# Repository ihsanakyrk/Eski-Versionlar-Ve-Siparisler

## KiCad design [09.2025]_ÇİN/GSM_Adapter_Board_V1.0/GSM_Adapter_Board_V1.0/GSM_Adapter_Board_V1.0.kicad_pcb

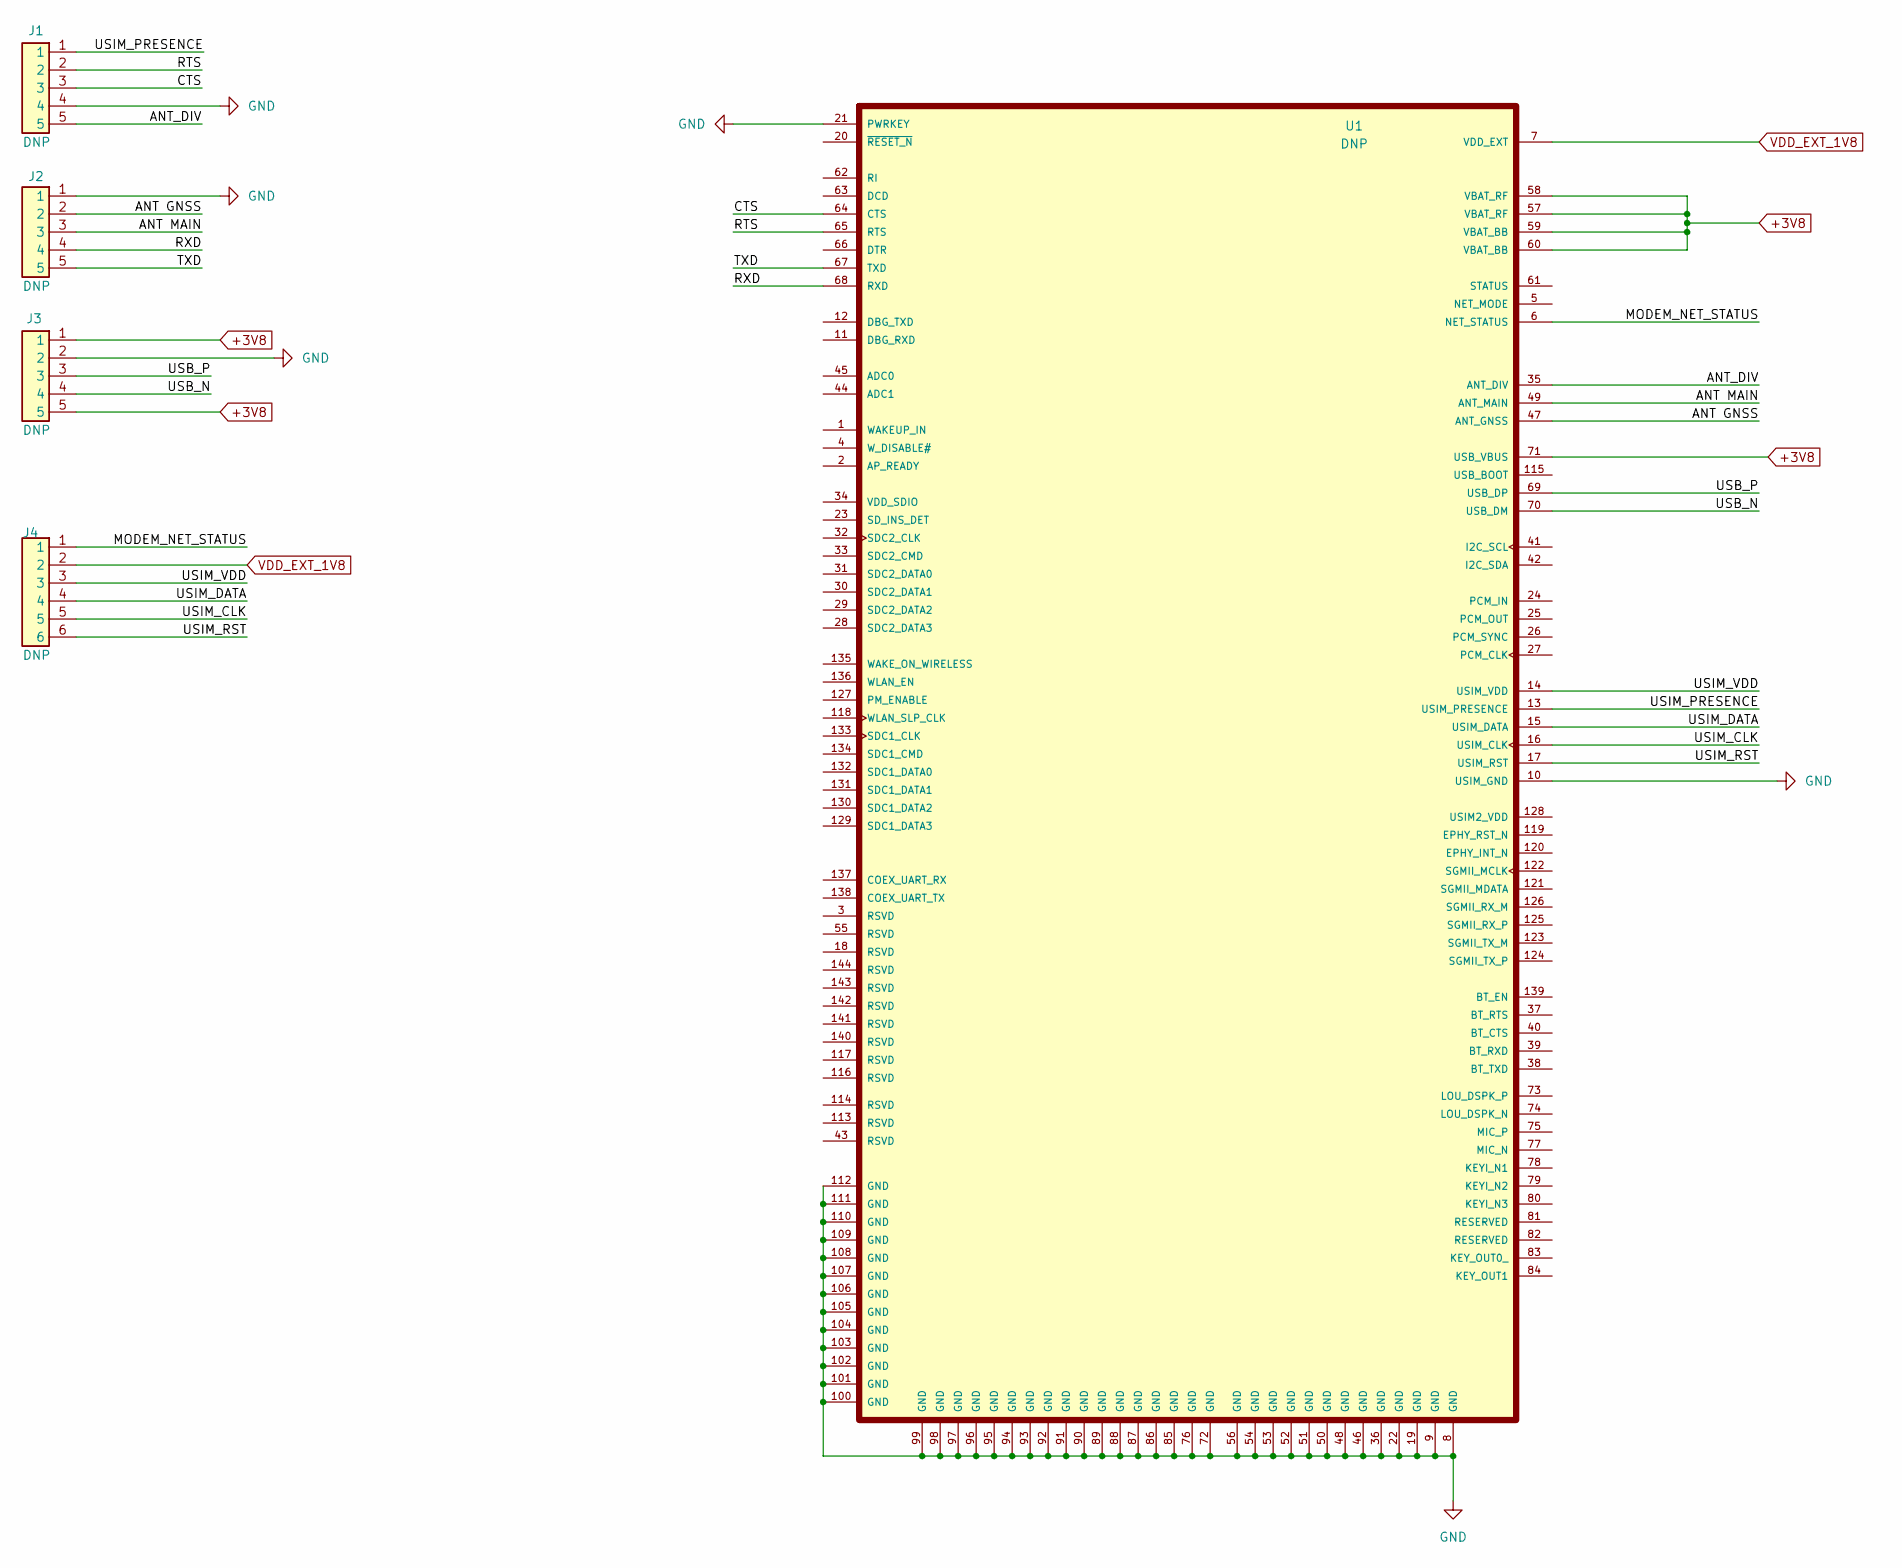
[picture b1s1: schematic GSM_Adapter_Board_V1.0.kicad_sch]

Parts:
J1, J2, J3: DNP; Castelled 5
J4: DNP; castelled 6
U1: DNP; GSM

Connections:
+3V8: J3.1, J3.5, U1.57 (VBAT_RF), U1.58 (VBAT_RF), U1.59 (VBAT_BB), U1.60 (VBAT_BB), U1.71 (USB_VBUS)
/ANT GNSS: J2.2, U1.47 (ANT_GNSS)
/ANT MAIN: J2.3, U1.49 (ANT_MAIN)
/ANT_DIV: J1.5, U1.35 (ANT_DIV)
/CTS: J1.3, U1.64 (CTS)
/MODEM_NET_STATUS: J4.1, U1.6 (NET_STATUS)
/RTS: J1.2, U1.65 (RTS)
/RXD: J2.4, U1.68 (RXD)
/TXD: J2.5, U1.67 (TXD)
/USB_N: J3.4, U1.70 (USB_DM)
/USB_P: J3.3, U1.69 (USB_DP)
/USIM_CLK: J4.5, U1.16 (USIM_CLK)
/USIM_DATA: J4.4, U1.15 (USIM_DATA)
/USIM_PRESENCE: J1.1, U1.13 (USIM_PRESENCE)
/USIM_RST: J4.6, U1.17 (USIM_RST)
/USIM_VDD: J4.3, U1.14 (USIM_VDD)
GND: J1.4, J2.1, J3.2, U1.8 (GND), U1.9 (GND), U1.10 (USIM_GND), U1.19 (GND), U1.21 (PWRKEY), U1.22 (GND), U1.36 (GND), U1.46 (GND), U1.48 (GND), U1.50 (GND), U1.51 (GND), U1.52 (GND), U1.53 (GND), U1.54 (GND), U1.56 (GND), U1.72 (GND), U1.76 (GND), U1.85 (GND), U1.86 (GND), U1.87 (GND), U1.88 (GND), U1.89 (GND), U1.90 (GND), U1.91 (GND), U1.92 (GND), U1.93 (GND), U1.94 (GND), U1.95 (GND), U1.96 (GND), U1.97 (GND), U1.98 (GND), U1.99 (GND), U1.100 (GND), U1.101 (GND), U1.102 (GND), U1.103 (GND), U1.104 (GND), U1.105 (GND), U1.106 (GND), U1.107 (GND), U1.108 (GND), U1.109 (GND), U1.110 (GND), U1.111 (GND), U1.112 (GND)
VDD_EXT_1V8: J4.2, U1.7 (VDD_EXT)

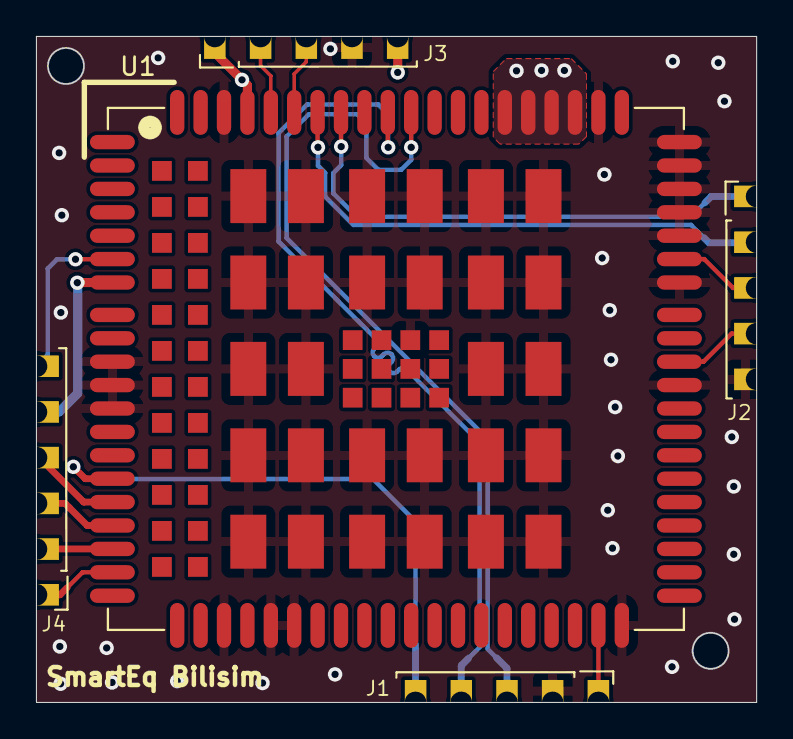
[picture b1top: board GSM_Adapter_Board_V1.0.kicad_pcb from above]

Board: 2 copper layers, 40.0 x 37.0 mm, 5 parts (0 on the bottom side), 18 nets.

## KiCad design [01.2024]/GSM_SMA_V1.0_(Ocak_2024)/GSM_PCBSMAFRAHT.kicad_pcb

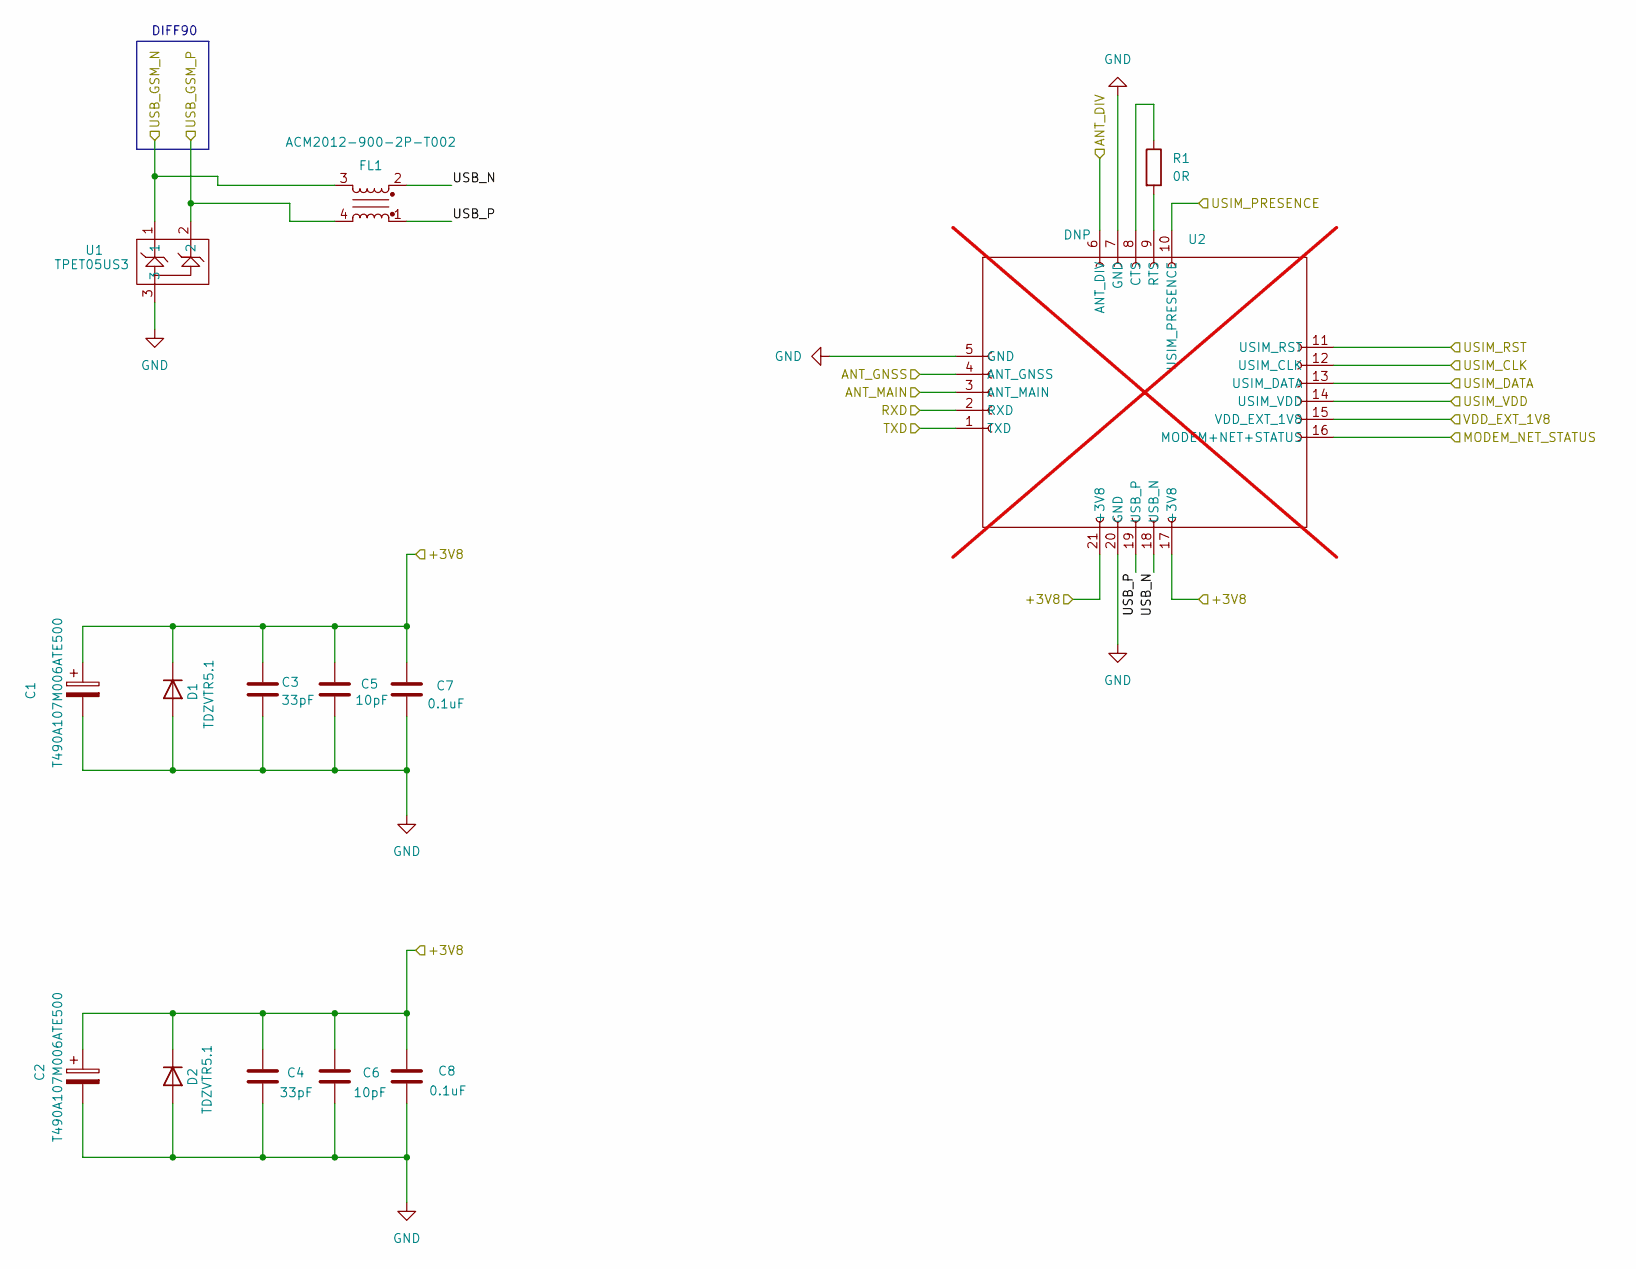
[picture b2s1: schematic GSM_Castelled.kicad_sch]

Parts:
C1, C2: T490A107M006ATE500; T490A; MPN T490A107M006ATE500
C3, C4: 33pF; C_0603_1608Metric
C5, C6: 10pF; C_0603_1608Metric
C7, C8: 0.1uF; C_0603_1608Metric
D1, D2: TDZVTR5.1; MPN TDZVTR5.1
FL1: ACM2012-900-2P-T002; MPN ACM2012-900-2P-T002
R1: 0R; R_0603_1608Metric
U1: TPET05US3; MPN TPET05US3
U2: DNP; GSM_Castelled; not fitted

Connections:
/91228-3002/MODEM_NET_STATUS: U2.16 (MODEM+NET+STATUS); also elsewhere on the board
/91228-3002/RXD: U2.2 (RXD); also elsewhere on the board
/91228-3002/TXD: U2.1 (TXD); also elsewhere on the board
/91228-3002/USB_GSM_N: FL1.3, U1.1; also elsewhere on the board
/91228-3002/USB_GSM_P: FL1.4, U1.2; also elsewhere on the board
/91228-3002/USIM_CLK: U2.12 (USIM_CLK); also elsewhere on the board
/91228-3002/USIM_DATA: U2.13 (USIM_DATA); also elsewhere on the board
/91228-3002/USIM_PRESENCE: U2.10 (USIM_PRESENCE); also elsewhere on the board
/91228-3002/USIM_RST: U2.11 (USIM_RST); also elsewhere on the board
/91228-3002/USIM_VDD: U2.14 (USIM_VDD); also elsewhere on the board
/91228-3002/VDD_EXT_1V8: U2.15 (VDD_EXT_1V8); also elsewhere on the board
/GSM_Castelled/+3V8: C1.1, C2.1, C3.1, C4.1, C5.1, C6.1, C7.1, C8.1, D1.1 (K), D2.1 (K), U2.17 (+3V8), U2.21 (+3V8); also elsewhere on the board
/GSM_Castelled/ANT_DIV: U2.6 (ANT_DIV); also elsewhere on the board
/GSM_Castelled/ANT_GNSS: U2.4 (ANT_GNSS); also elsewhere on the board
/GSM_Castelled/ANT_MAIN: U2.3 (ANT_MAIN); also elsewhere on the board
/GSM_Castelled/USB_N: FL1.2, U2.18 (USB_N)
/GSM_Castelled/USB_P: FL1.1, U2.19 (USB_P)
GND: C1.2, C2.2, C3.2, C4.2, C5.2, C6.2, C7.2, C8.2, D1.2 (A), D2.2 (A), U1.3, U2.5 (GND), U2.7 (GND), U2.20 (GND); also elsewhere on the board
unnamed: R1.1, U2.8 (CTS)
unnamed: R1.2, U2.9 (RTS)

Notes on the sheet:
DIFF90

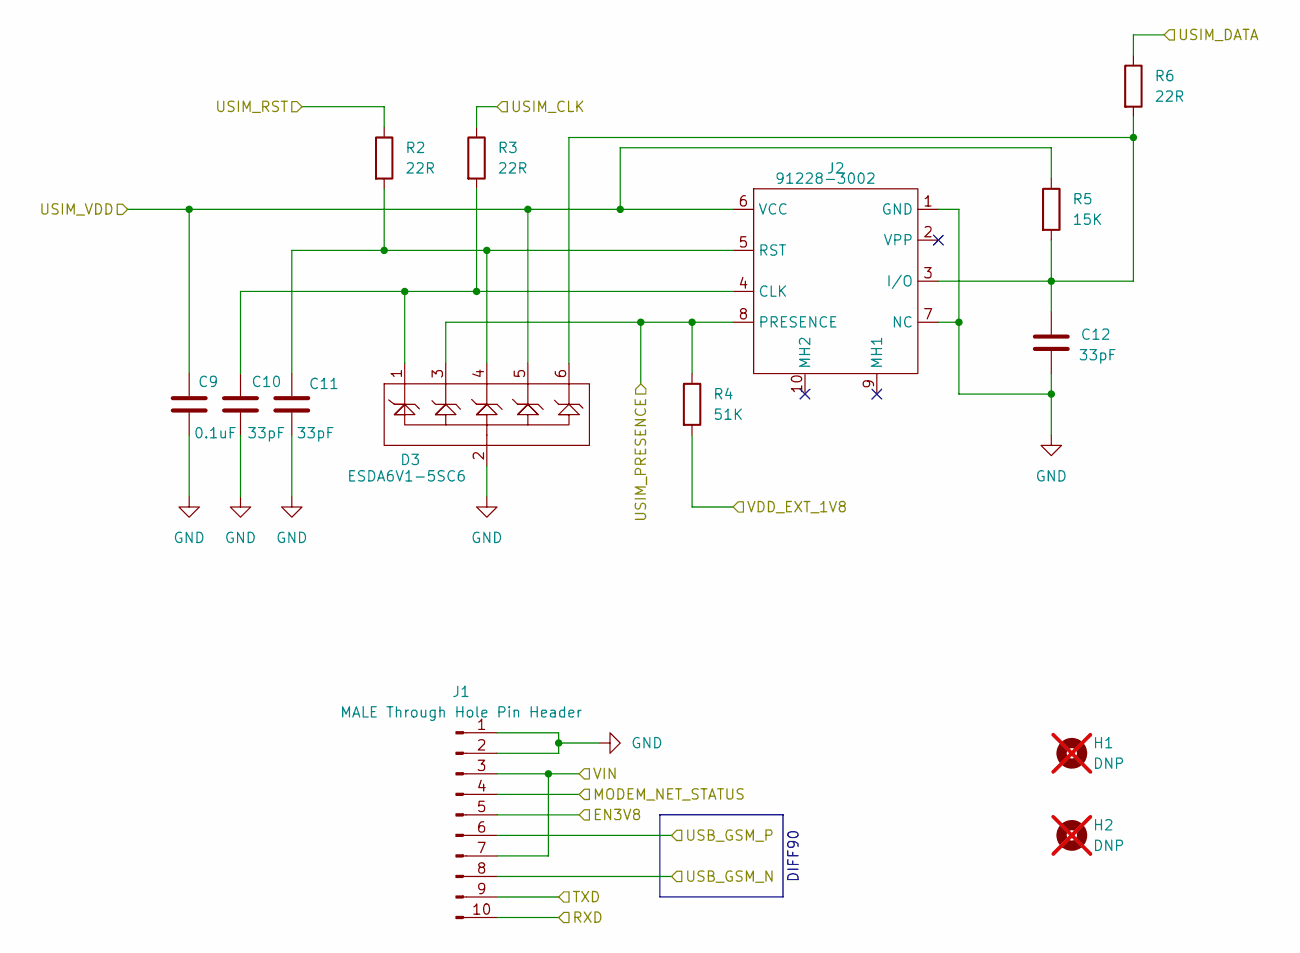
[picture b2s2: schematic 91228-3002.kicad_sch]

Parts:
C9: 0.1uF; C_0603_1608Metric
C10, C11, C12: 33pF; C_0603_1608Metric
D3: ESDA6V1-5SC6; MPN ESDA6V1-5SC6
H1, H2: DNP; Screw_Terminal_1x1; not fitted
J1: MALE Through Hole Pin Header; PinHeader_2x05_P2.00mm_Vertical
J2: 91228-3002; 912283002; MPN 91228-3002
R2, R3, R6: 22R; R_0603_1608Metric
R4: 51K; R_0603_1608Metric
R5: 15K; R_0603_1608Metric

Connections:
/91228-3002/EN3V8: J1.5; also elsewhere on the board
/91228-3002/MODEM_NET_STATUS: J1.4; also elsewhere on the board
/91228-3002/RXD: J1.10; also elsewhere on the board
/91228-3002/TXD: J1.9; also elsewhere on the board
/91228-3002/USB_GSM_N: J1.8; also elsewhere on the board
/91228-3002/USB_GSM_P: J1.6; also elsewhere on the board
/91228-3002/USIM_CLK: R3.1; also elsewhere on the board
/91228-3002/USIM_DATA: R6.1; also elsewhere on the board
/91228-3002/USIM_PRESENCE: D3.3, J2.8 (PRESENCE), R4.1; also elsewhere on the board
/91228-3002/USIM_RST: R2.1; also elsewhere on the board
/91228-3002/USIM_VDD: C9.1, D3.5, J2.6 (VCC), R5.1; also elsewhere on the board
/91228-3002/VDD_EXT_1V8: R4.2; also elsewhere on the board
/91228-3002/VIN: J1.3, J1.7; also elsewhere on the board
GND: C9.2, C10.2, C11.2, C12.2, D3.2, J1.1, J1.2, J2.1 (GND), J2.7 (NC); also elsewhere on the board
unnamed: C10.1, D3.1, J2.4 (CLK), R3.2
unnamed: C12.1, D3.6, J2.3 (I/O), R5.2, R6.2
unnamed: C11.1, D3.4, J2.5 (RST), R2.2

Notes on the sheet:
DIFF90

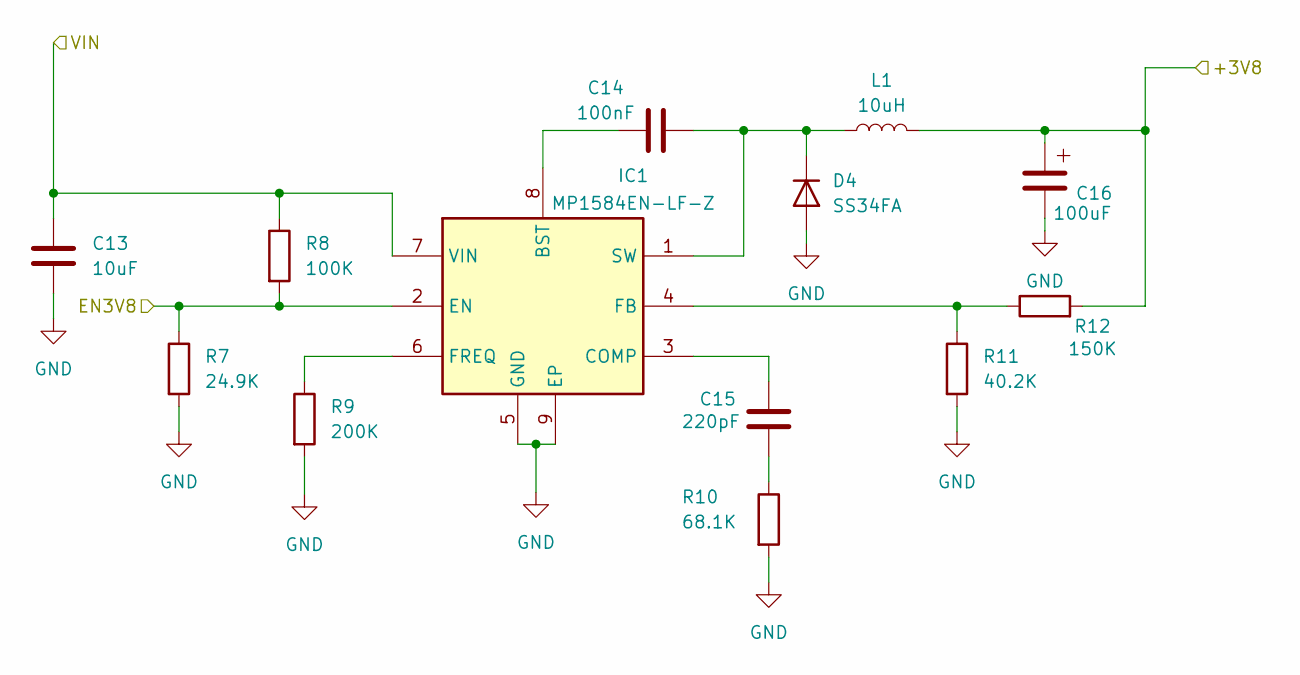
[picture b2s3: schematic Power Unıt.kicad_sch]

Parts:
C13: 10uF; C_1206_3216Metric
C14: 100nF; C_0603_1608Metric
C15: 220pF; C_0603_1608Metric
C16: 100uF; CP_Elec_5x5.4; MPN UWR1A101MCL1GB
D4: SS34FA; SS4FA; MPN SS34FA
IC1: MP1584EN-LF-Z; Manufacturer_Part_Number MP1584EN
L1: 10uH; L_7.3x7.3_H3.5; MPN CDRH74NP-100MC-B
R7: 24.9K; R_0603_1608Metric
R8: 100K; R_0603_1608Metric
R9: 200K; R_0603_1608Metric
R10: 68.1K; R_0603_1608Metric
R11: 40.2K; R_0603_1608Metric
R12: 150K; R_0603_1608Metric

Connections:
/91228-3002/EN3V8: IC1.2 (EN), R7.1, R8.2; also elsewhere on the board
/91228-3002/VIN: C13.1, IC1.7 (VIN), R8.1; also elsewhere on the board
/GSM_Castelled/+3V8: C16.1, L1.2, R12.2; also elsewhere on the board
GND: C13.2, C16.2, D4.2 (A), IC1.5 (GND), IC1.9 (EP), R7.2, R9.2, R10.2, R11.2; also elsewhere on the board
unnamed: C15.2, R10.1
unnamed: C14.2, D4.1 (K), IC1.1 (SW), L1.1
unnamed: C14.1, IC1.8 (BST)
unnamed: C15.1, IC1.3 (COMP)
unnamed: IC1.4 (FB), R11.1, R12.1
unnamed: IC1.6 (FREQ), R9.1

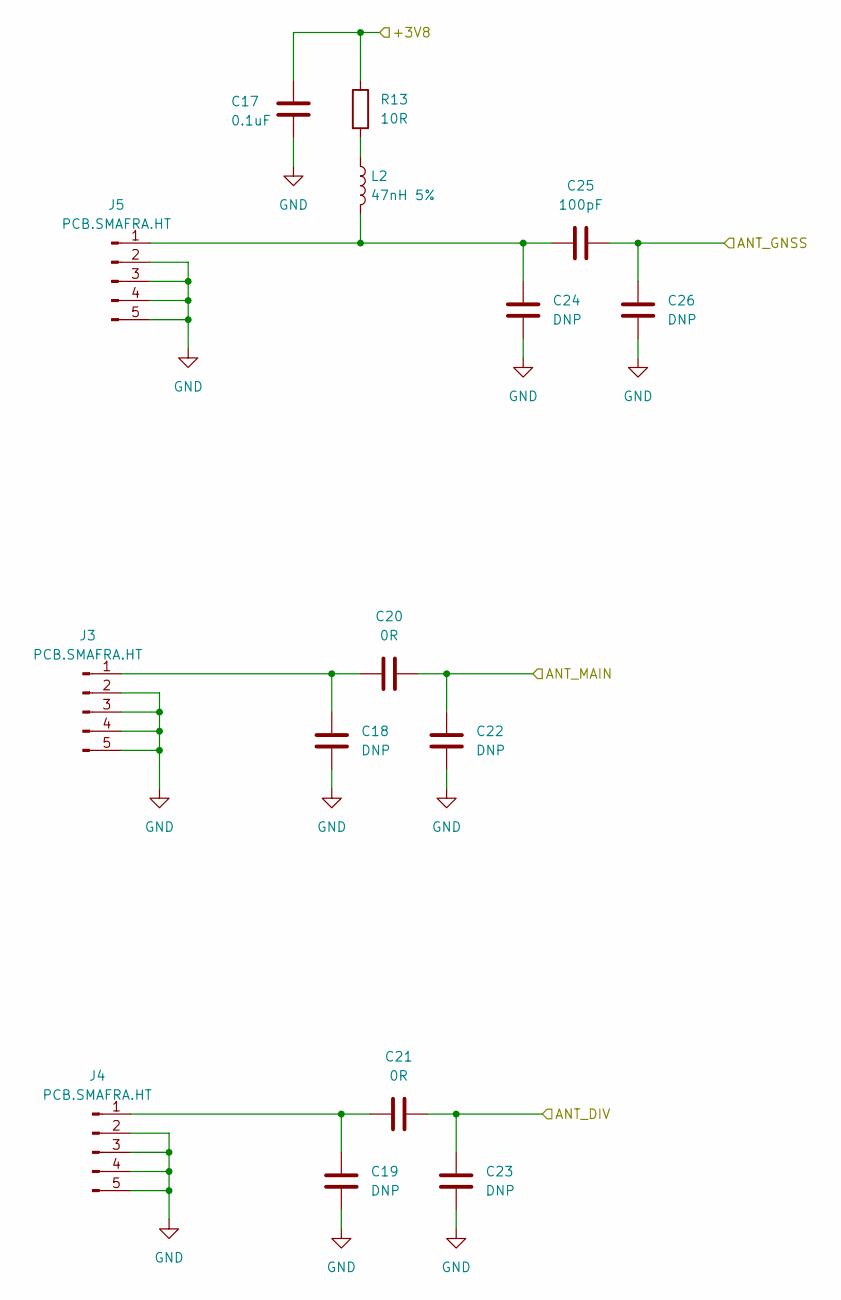
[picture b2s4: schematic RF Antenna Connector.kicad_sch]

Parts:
C17: 0.1uF; C_0603_1608Metric
C18, C19, C22, C23, C24, C26: DNP; C_0603_1608Metric
C20, C21: 0R; C_0603_1608Metric
C25: 100pF; C_0603_1608Metric
J3, J4, J5: PCB.SMAFRA.HT
L2: 47nH 5%; L_0402_1005Metric; MPN LQG15HS47NJ02D
R13: 10R; R_0603_1608Metric

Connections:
/GSM_Castelled/+3V8: C17.1, R13.1; also elsewhere on the board
/GSM_Castelled/ANT_DIV: C20.2, C22.1; also elsewhere on the board
/GSM_Castelled/ANT_GNSS: C25.2, C26.1; also elsewhere on the board
/GSM_Castelled/ANT_MAIN: C21.2, C23.1; also elsewhere on the board
GND: C17.2, C18.1, C19.1, C22.2, C23.2, C24.1, C26.2, J3.2, J3.3, J3.4, J3.5, J4.2, J4.3, J4.4, J4.5, J5.2, J5.3, J5.4, J5.5; also elsewhere on the board
unnamed: C18.2, C20.1, J3.1
unnamed: C19.2, C21.1, J4.1
unnamed: C24.2, C25.1, J5.1, L2.2
unnamed: L2.1, R13.2

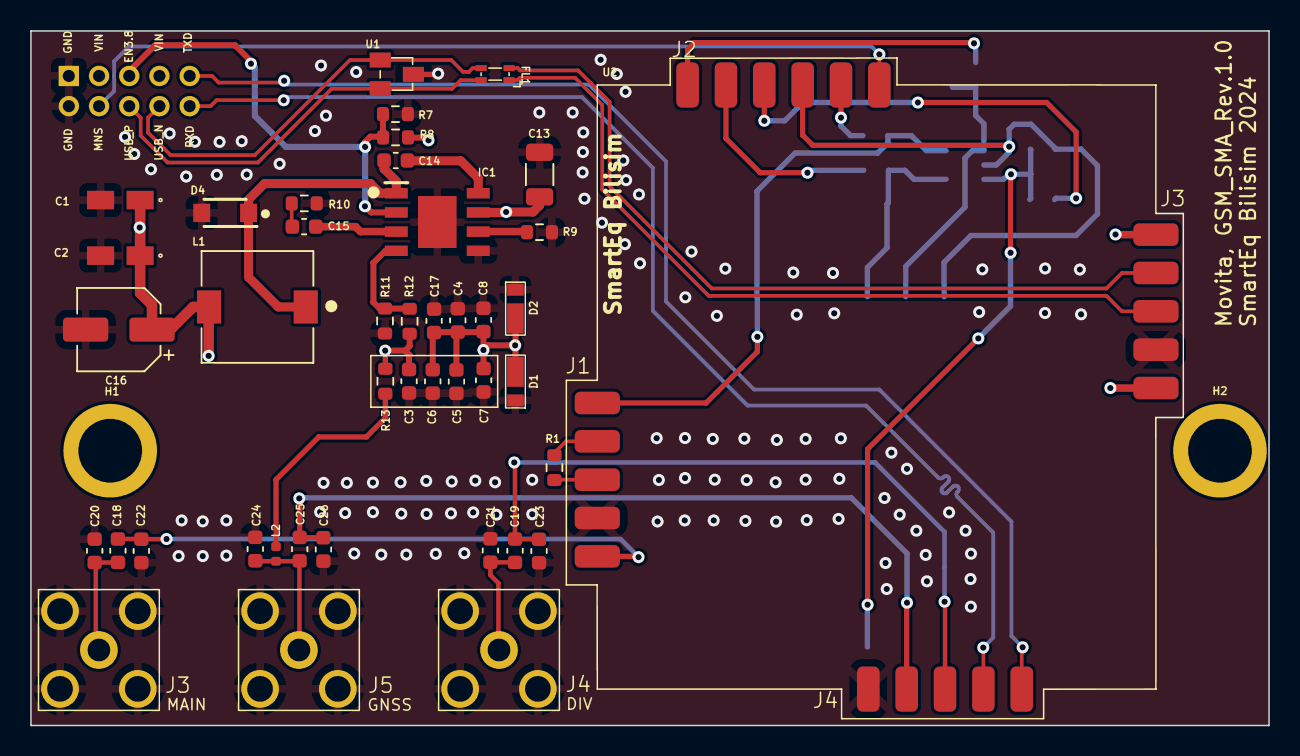
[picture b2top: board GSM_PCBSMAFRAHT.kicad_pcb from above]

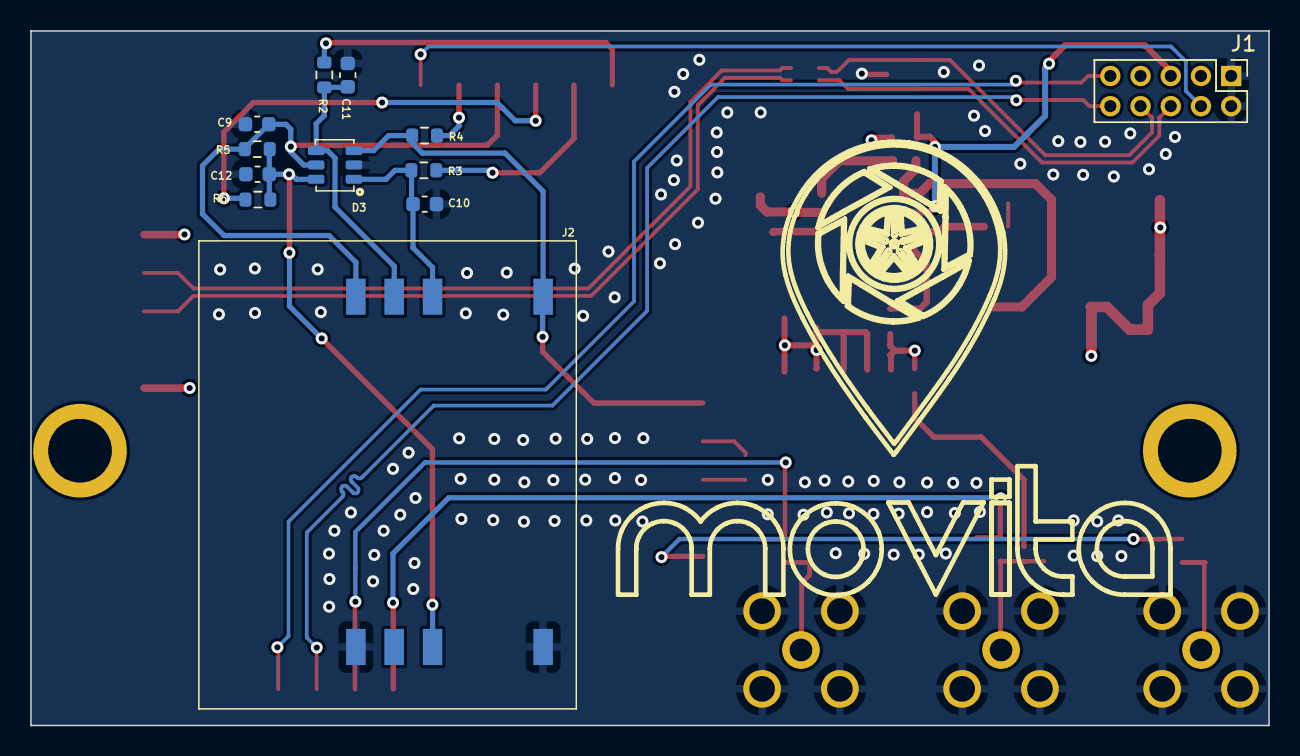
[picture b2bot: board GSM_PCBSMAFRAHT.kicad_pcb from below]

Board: 4 copper layers, 82.0 x 46.0 mm, 56 parts (12 on the bottom side), 35 nets.

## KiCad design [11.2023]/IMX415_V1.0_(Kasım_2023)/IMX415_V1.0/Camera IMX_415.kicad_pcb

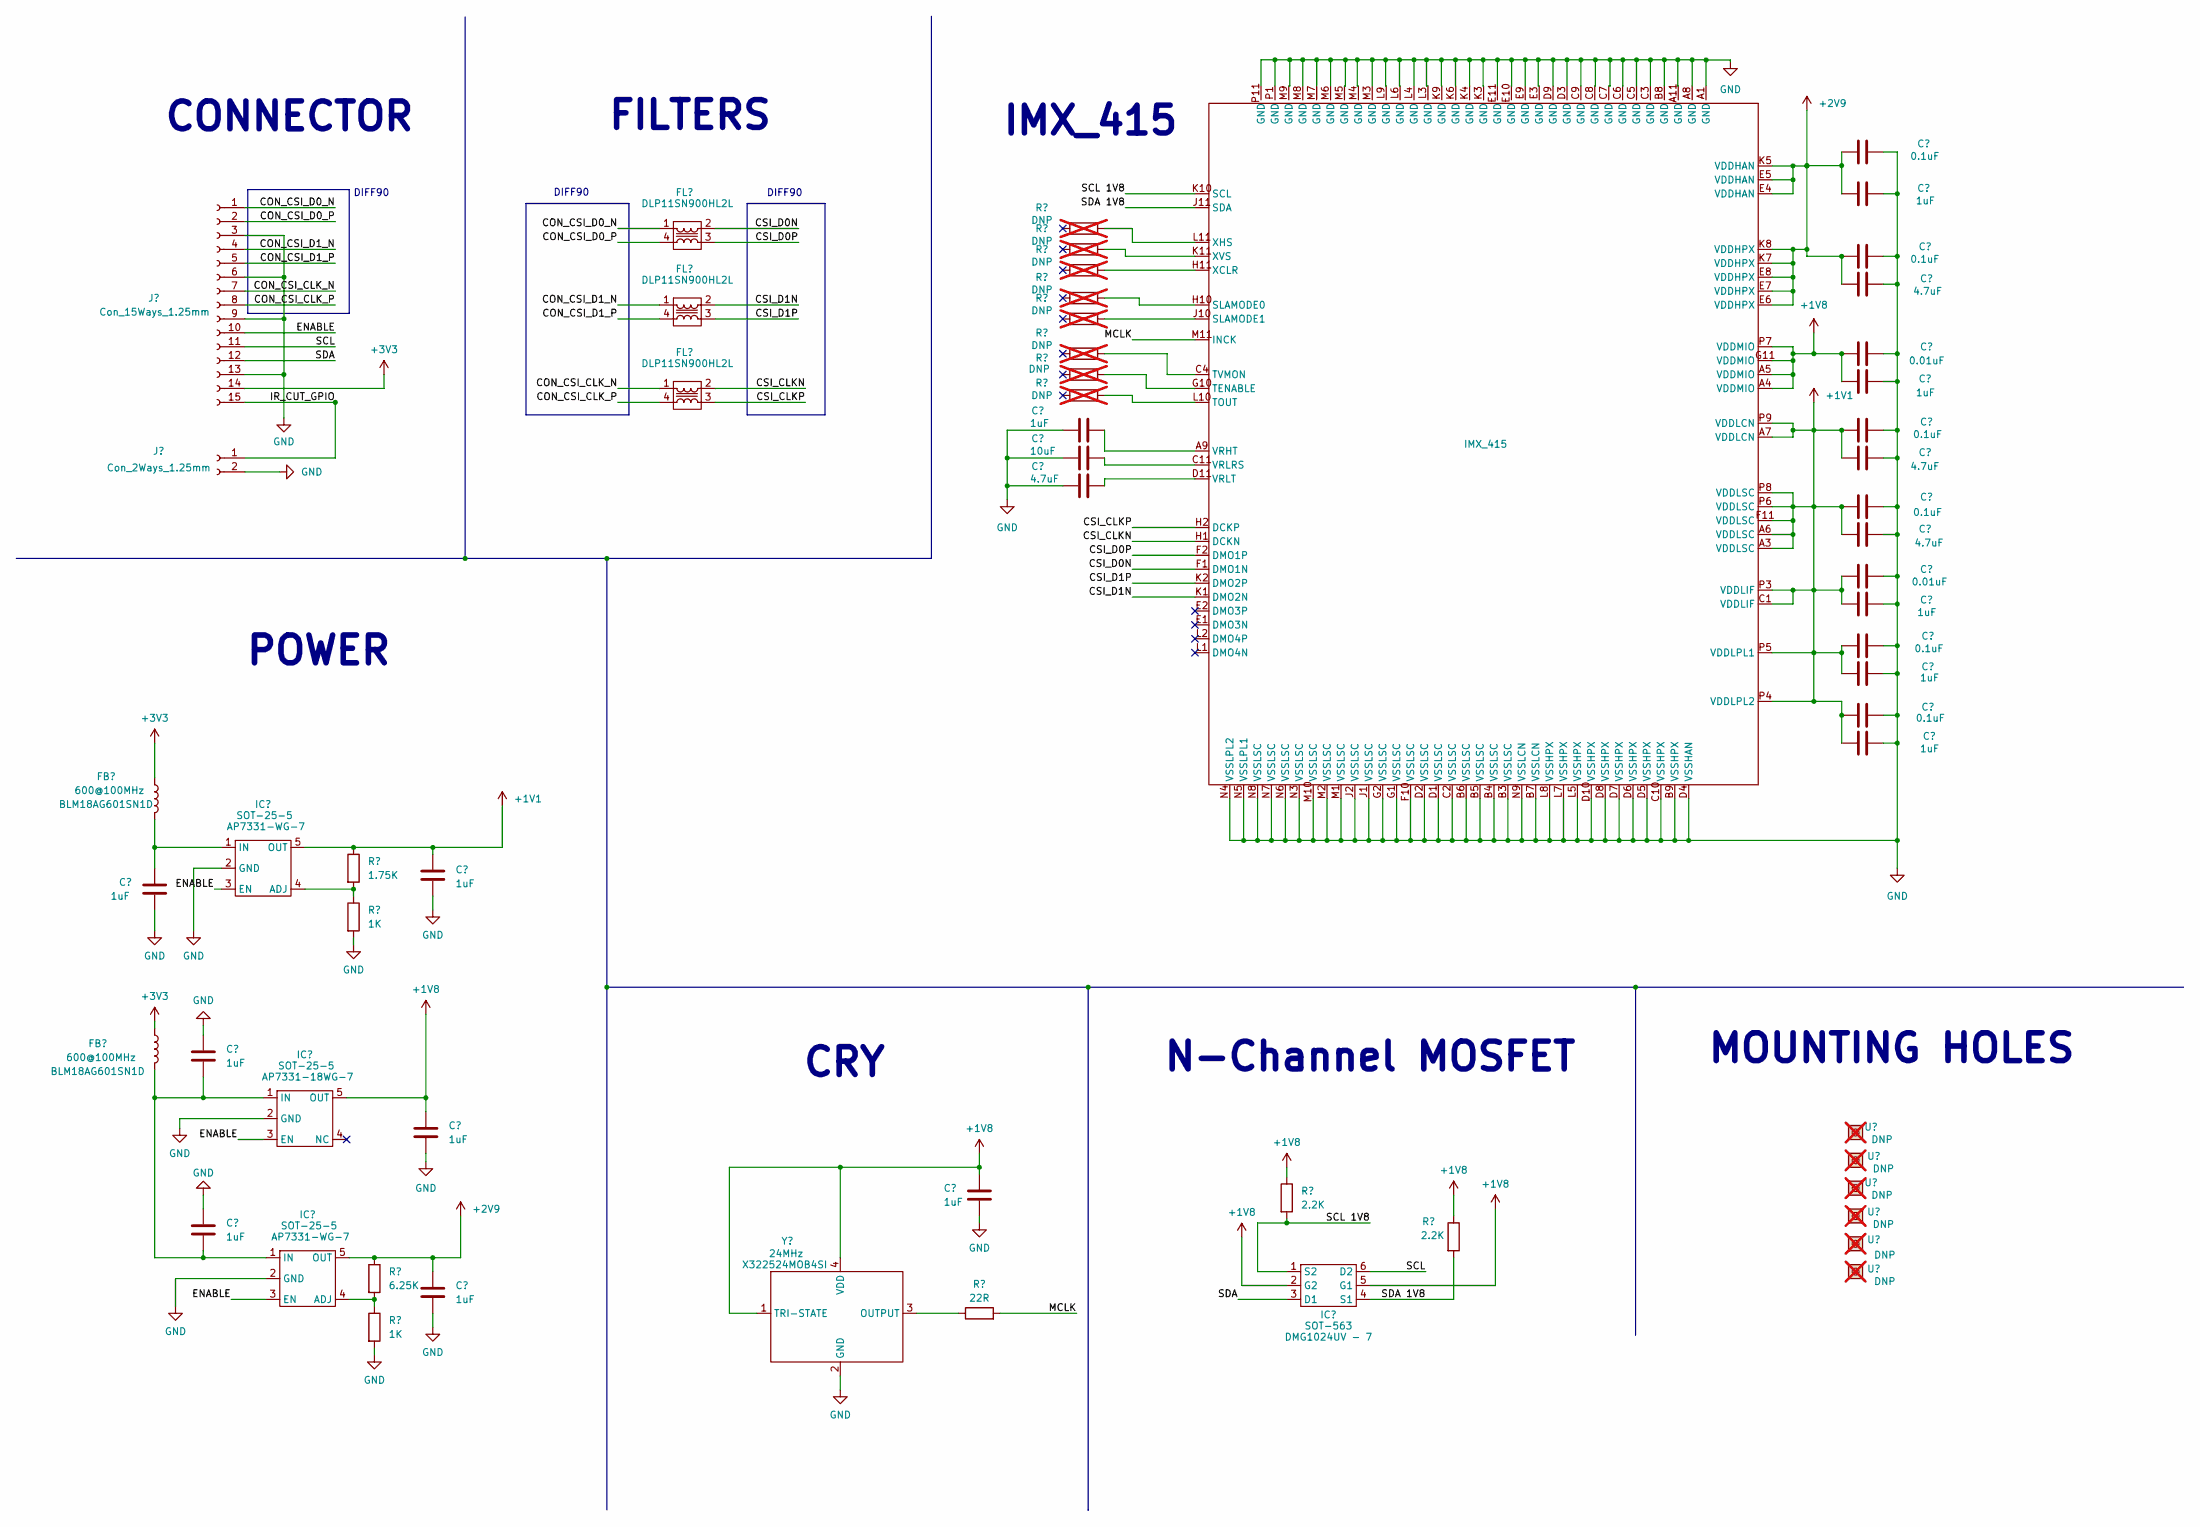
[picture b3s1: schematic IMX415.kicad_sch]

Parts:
C1, C2, C3, C4, C5, C6, C7, C8, C12, C16, C22, C24, C26: 1uF; C_0402_1005Metric
C9: 10uF; C_0402_1005Metric
C10, C14, C18, C20: 4.7uF; C_0402_1005Metric
C11, C13, C17, C19, C23, C25: 0.1uF; C_0402_1005Metric
C15, C21: 0.01uF; C_0402_1005Metric
FB1, FB2: 600@100MHz; BLM18AG601SN1D; MPN BLM18AG601SN1D
FL1, FL2, FL3: DLP11SN900HL2L; MPN DLP11SN900HL2L
IC1, IC3: SOT-25-5; AP7331; MPN AP7331-WG-7
IC2: SOT-25-5; AP7331; MPN AP7331-18WG-7
IC4: SOT-563; DMG1024UV - 7; MPN DMG1024UV - 7
IC5: IMX_415; MPN IMX_415
J1: Con_15Ways_1.25mm; JST_1x15-1MP_P1.25mm_Horizontal
J2: Con_2Ways_1.25mm; MPN WAFER-MX125Z-2A
R1: 1.75K; R_0402_1005Metric
R2, R4: 1K; R_0402_1005Metric
R3: 6.25K; R_0402_1005Metric
R5: 22R; R_0402_1005Metric
R6, R7, R8, R9, R10, R11, R12, R13: DNP; R_0402_1005Metric; not fitted
R14, R15: 2.2K; R_0402_1005Metric
U1, U2, U3, U4, U5, U6: DNP; Screw_Terminal_1x1; not fitted
Y1: 24MHz; X322524MOB4SI; MPN X322524MOB4SI

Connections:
+1V1: C5.1, C17.2, C18.2, C19.2, C20.2, C21.2, C22.2, C23.2, C24.2, C25.2, C26.2, IC1.5 (OUT), IC5.A3 (VDDLSC), IC5.A6 (VDDLSC), IC5.A7 (VDDLCN), IC5.C1 (VDDLIF), IC5.F11 (VDDLSC), IC5.P3 (VDDLIF), IC5.P4 (VDDLPL2), IC5.P5 (VDDLPL1), IC5.P6 (VDDLSC), IC5.P8 (VDDLSC), IC5.P9 (VDDLCN), R1.1
+1V8: C4.1, C7.1, C15.2, C16.2, IC2.5 (OUT), IC4.2 (G2), IC4.5 (G1), IC5.A4 (VDDMIO), IC5.A5 (VDDMIO), IC5.G11 (VDDMIO), IC5.P7 (VDDMIO), R14.1, R15.1, Y1.1 (TRI-STATE), Y1.4 (VDD)
+2V9: C6.1, C11.2, C12.2, C13.2, C14.2, IC3.5 (OUT), IC5.E4 (VDDHAN), IC5.E5 (VDDHAN), IC5.E6 (VDDHPX), IC5.E7 (VDDHPX), IC5.E8 (VDDHPX), IC5.K5 (VDDHAN), IC5.K7 (VDDHPX), IC5.K8 (VDDHPX), R3.1
+3V3: FB1.1, FB2.1, J1.14
/IMX415/CON_CSI_CLK_N: FL3.1, J1.7
/IMX415/CON_CSI_CLK_P: FL3.4, J1.8
/IMX415/CON_CSI_D0_N: FL1.1, J1.1
/IMX415/CON_CSI_D0_P: FL1.4, J1.2
/IMX415/CON_CSI_D1_N: FL2.1, J1.4
/IMX415/CON_CSI_D1_P: FL2.4, J1.5
/IMX415/CSI_CLKN: FL3.2, IC5.H1 (DCKN)
/IMX415/CSI_CLKP: FL3.3, IC5.H2 (DCKP)
/IMX415/CSI_D0N: FL1.2, IC5.F1 (DMO1N)
/IMX415/CSI_D0P: FL1.3, IC5.F2 (DMO1P)
/IMX415/CSI_D1N: FL2.2, IC5.K1 (DMO2N)
/IMX415/CSI_D1P: FL2.3, IC5.K2 (DMO2P)
/IMX415/ENABLE: IC1.3 (EN), IC2.3 (EN), IC3.3 (EN), J1.10
/IMX415/IR_CUT_GPIO: J1.15, J2.1
/IMX415/MCLK: IC5.M11 (INCK), R5.2
/IMX415/SCL: IC4.6 (D2), J1.11
/IMX415/SCL 1V8: IC4.1 (S2), IC5.K10 (SCL), R14.2
/IMX415/SDA: IC4.3 (D1), J1.12
/IMX415/SDA 1V8: IC4.4 (S1), IC5.J11 (SDA), R15.2
GND: C1.2, C2.1, C3.1, C4.2, C5.2, C6.2, C7.2, C8.2, C9.2, C10.2, C11.1, C12.1, C13.1, C14.1, C15.1, C16.1, C17.1, C18.1, C19.1, C20.1, C21.1, C22.1, C23.1, C24.1, C25.1, C26.1, IC1.2 (GND), IC2.2 (GND), IC3.2 (GND), IC5.A1 (GND), IC5.A8 (GND), IC5.A11 (GND), IC5.B3 (VSSLSC), IC5.B4 (VSSLSC), IC5.B5 (VSSLSC), IC5.B6 (VSSLSC), IC5.B7 (VSSLCN), IC5.B8 (GND), IC5.B9 (VSSHPX), IC5.C2 (VSSLSC), IC5.C3 (GND), IC5.C5 (GND), IC5.C6 (GND), IC5.C7 (GND), IC5.C8 (GND), IC5.C9 (GND), IC5.C10 (VSSHPX), IC5.D1 (VSSLSC), IC5.D2 (VSSLSC), IC5.D3 (GND), IC5.D4 (VSSHAN), IC5.D5 (VSSHPX), IC5.D6 (VSSHPX), IC5.D7 (VSSHPX), IC5.D8 (VSSHPX), IC5.D9 (GND), IC5.D10 (VSSHPX), IC5.E3 (GND), IC5.E9 (GND), IC5.E10 (GND), IC5.E11 (GND), IC5.F10 (VSSLSC), IC5.G1 (VSSLSC), IC5.G2 (VSSLSC), IC5.J1 (VSSLSC), IC5.J2 (VSSLSC), IC5.K3 (GND), IC5.K4 (GND), IC5.K6 (GND), IC5.K9 (GND), IC5.L3 (GND), IC5.L4 (GND), IC5.L5 (VSSHPX), IC5.L6 (GND), IC5.L7 (VSSHPX), IC5.L8 (VSSHPX), IC5.L9 (GND), IC5.M1 (VSSLSC), IC5.M2 (VSSLSC), IC5.M3 (GND), IC5.M4 (GND), IC5.M5 (GND), IC5.M6 (GND), IC5.M7 (GND), IC5.M8 (GND), IC5.M9 (GND), IC5.M10 (VSSLSC), IC5.N3 (VSSLSC), IC5.N4 (VSSLPL2), IC5.N5 (VSSLPL1), IC5.N6 (VSSLSC), IC5.N7 (VSSLSC), IC5.N8 (VSSLSC), IC5.N9 (VSSLCN), IC5.P1 (GND), IC5.P11 (GND), J1.3, J1.6, J1.9, J1.13, J2.2, R2.2, R4.2, Y1.2 (GND)
unnamed: IC1.4 (ADJ), R1.2, R2.1
unnamed: C1.1, FB1.2, IC1.1 (IN)
unnamed: C2.2, C3.2, FB2.2, IC2.1 (IN), IC3.1 (IN)
unnamed: IC3.4 (ADJ), R3.2, R4.1
unnamed: IC5.H10 (SLAMODE0), R9.2
unnamed: IC5.J10 (SLAMODE1), R10.2
unnamed: IC5.G10 (TENABLE), R12.1
unnamed: IC5.L10 (TOUT), R13.2
unnamed: IC5.C4 (TVMON), R11.2
unnamed: C8.1, IC5.A9 (VRHT)
unnamed: C9.1, IC5.C11 (VRLRS)
unnamed: C10.1, IC5.D11 (VRLT)
unnamed: IC5.H11 (XCLR), R8.2
unnamed: IC5.L11 (XHS), R6.2
unnamed: IC5.K11 (XVS), R7.2
unnamed: R5.1, Y1.3 (OUTPUT)

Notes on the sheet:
DIFF90
N-Channel MOSFET
CRY
FILTERS
POWER
MOUNTING HOLES
CONNECTOR
IMX_415

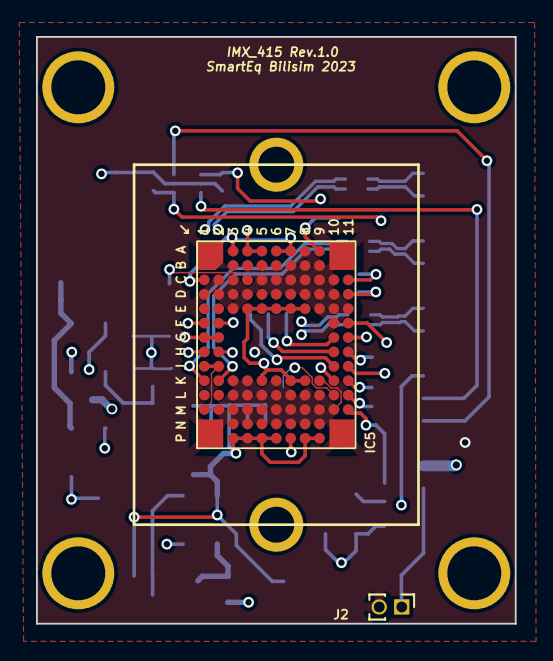
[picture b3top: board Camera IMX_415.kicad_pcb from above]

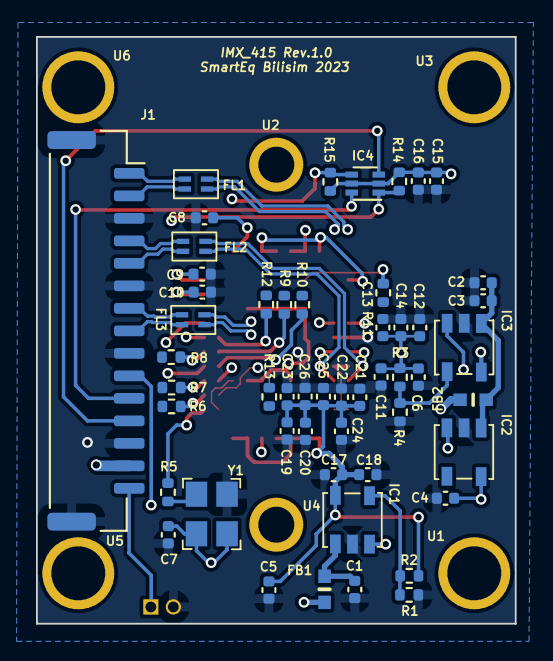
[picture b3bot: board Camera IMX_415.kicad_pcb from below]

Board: 4 copper layers, 26.6 x 32.6 mm, 60 parts (52 on the bottom side), 40 nets.

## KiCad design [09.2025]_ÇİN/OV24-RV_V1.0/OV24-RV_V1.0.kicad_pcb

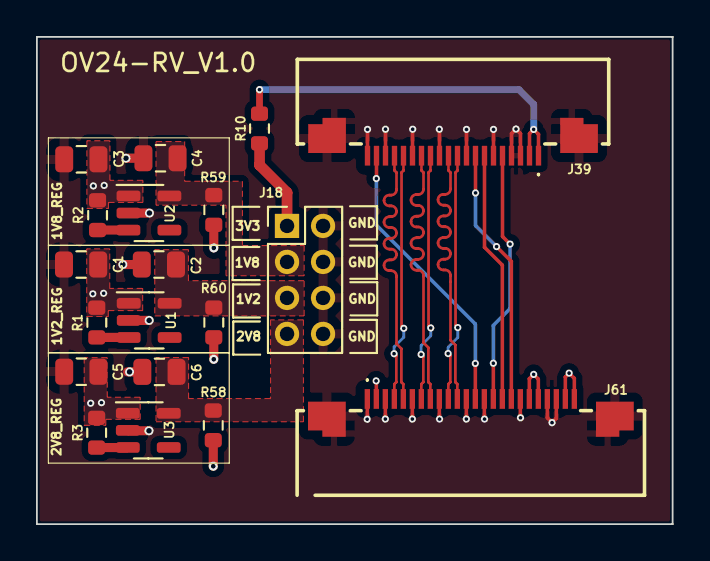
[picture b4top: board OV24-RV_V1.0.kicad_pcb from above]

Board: 2 copper layers, 35.3 x 27.1 mm, 19 parts (0 on the bottom side), 22 nets.

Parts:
C1, C2, C3, C4, C5, C6: 10uF; C_0805_2012Metric
J18: DNP; PinHeader_2x04_P2.00mm_Vertical
J39: FFC SOCKET DR_BOTTOM 0.5MM -20P; F32R1A7H111020
J61: FFC SOCKET DR_BOTTOM 0.5MM -24P; F32R1A7H111024
R1, R2, R3: 5K; R_0603_1608Metric
R10, R58, R59, R60: 0R; R_0603_1608Metric
U1: RT9080-12GJ5; SOT-23-5
U2: RT9080-18GJ5; SOT-23-5
U3: RT9080-28GJ5; SOT-23-5

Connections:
/+3V3: J39.1, J39.2, R10.2
/MIPI_I2C_SCL: J39.8, J61.17
/MIPI_I2C_SDA: J39.7, J61.16
/MIPI_LVDS_CLK_N: J39.13, J61.7
/MIPI_LVDS_CLK_P: J39.14, J61.8
/MIPI_LVDS_D0_N: J39.16, J61.4
/MIPI_LVDS_D0_P: J39.17, J61.5
/MIPI_LVDS_D1_N: J39.10, J61.10
/MIPI_LVDS_D1_P: J39.11, J61.11
/MIPI_LVDS_MCLK0: J39.19, J61.13
/MIPI_LVDS_RST: J39.5, J61.15
AVDD2V8: C6.1, J18.7, R58.1, U3.5 (OUT)
DOVDD1V8: C4.1, J18.3, R59.1, U2.5 (OUT)
DVDD1V2: C2.1, J18.5, R60.1, U1.5 (OUT)
GND: C1.2, C2.2, C3.2, C4.2, C5.2, C6.2, J18.2, J18.4, J18.6, J18.8, J39.3, J39.4, J39.6, J39.9, J39.12, J39.15, J39.18, J39.20, J39.21, J39.22, J61.1, J61.3, J61.6, J61.9, J61.12, J61.14, J61.18, J61.21, J61.22, J61.25, J61.26, U1.2 (GND), U2.2 (GND), U3.2 (GND)
unnamed: J61.2, R59.2
unnamed: J61.19, J61.20, R60.2
unnamed: J61.23, J61.24, R58.2
unnamed: R1.2, U1.3 (EN)
unnamed: R2.2, U2.3 (EN)
unnamed: R3.2, U3.3 (EN)
VCC_3V3: C1.1, C3.1, C5.1, J18.1, R1.1, R2.1, R3.1, R10.1, U1.1 (IN), U2.1 (IN), U3.1 (IN)
